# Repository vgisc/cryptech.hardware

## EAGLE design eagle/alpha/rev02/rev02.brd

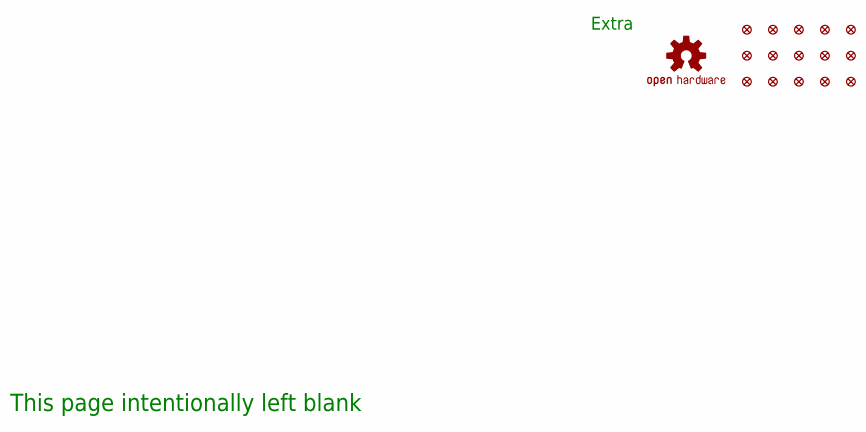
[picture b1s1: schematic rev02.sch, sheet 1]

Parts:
FID1, FID2, FID3, FID4, FID5, FID6, FID7, FID8, FID9, FID10, FID11, FID12, FID13, FID14, FID15: FIDUCIAL1X2; FIDUCIAL-1X2
LOGO1: OSHW-LOGOL-COPPER; OSHW-LOGO-L_COPPER

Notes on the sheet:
Extra
This page intentionally left blank

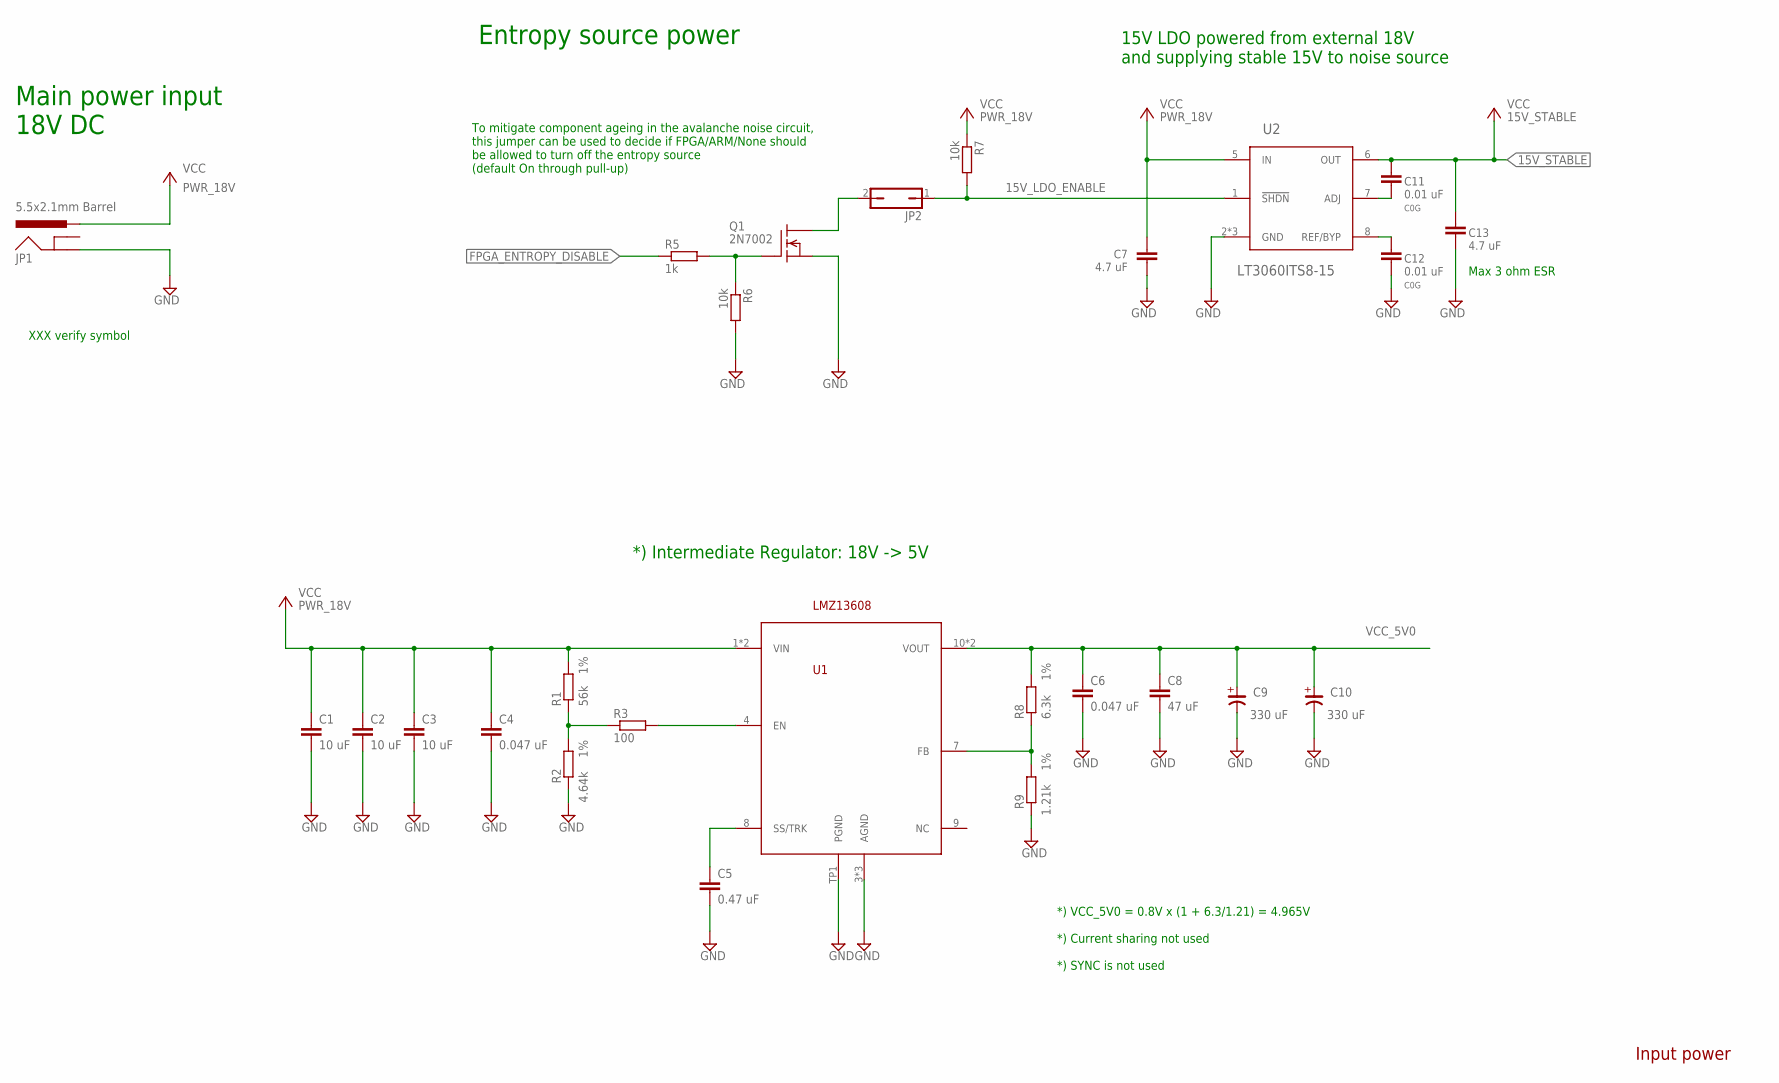
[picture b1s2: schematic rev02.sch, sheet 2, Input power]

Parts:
C1, C2, C3: 10 uF; C1210; TOLERANCE 10%
C4, C6: 0.047 uF; C0402; TOLERANCE 10%
C5: 0.47 uF; C0603; TOLERANCE 10%
C7, C13: 4.7 uF; C0603
C8: 47 uF; C1210; TOLERANCE 20%
C9, C10: 330 uF; CE-035X080; TOLERANCE 20%
C11, C12: 0.01 uF; C0402
JP1: 5.5x2.1mm Barrel; POWER_JACK_SMD
JP2: JP1Q; JP1
Q1: 2N7002; SOT23
R1: 56k; R0402; TOLERANCE 1%
R2: 4.64k; R0402; TOLERANCE 1%
R3: 100; R0402; TOLERANCE 5%
R5: 1k; R0402; TOLERANCE 5%
R6, R7: 10k; R0402; TOLERANCE 5%
R8: 6.3k; R0402; TOLERANCE 1%
R9: 1.21k; R0402; TOLERANCE 1%
U1: LMZ13608; NDY
U2: LT3060ITS8-15; TSOT-8-23

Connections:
15V_LDO_ENABLE: JP2.1, R7.2, U2.1 (!SHDN)
15V_STABLE: C11.2, C13.1, U2.6 (OUT); also elsewhere on the board
FPGA_ENTROPY_DISABLE: R5.1; also elsewhere on the board
GND: C1.2, C2.2, C3.2, C4.2, C5.2, C6.2, C7.2, C8.2, C9.-, C10.-, C12.1, C13.2, JP1.P$4 (GND), Q1.2 (S), R2.1, R6.2, R9.1, U1.3 (AGND), U1.5 (AGND), U1.6 (AGND), U1.TP1 (PGND), U2.2 (GND), U2.3 (GND), U2.4 (GND); also elsewhere on the board
unnamed: C11.1, U2.7 (ADJ)
unnamed: C12.2, U2.8 (REF/BYP)
unnamed: Q1.1 (G), R5.2, R6.1
unnamed: JP2.2, Q1.3 (D)
unnamed: C5.1, U1.8 (SS/TRK)
unnamed: R1.1, R2.2, R3.1
unnamed: R3.2, U1.4 (EN)
unnamed: R8.1, R9.2, U1.7 (FB)
PWR_18V: C1.1, C2.1, C3.1, C4.1, C7.1, JP1.VIN0 (PWR), R1.2, R7.1, U1.1 (VIN), U1.2 (VIN), U2.5 (IN)
VCC_5V0: C6.1, C8.1, C9.+, C10.+, R8.2, U1.10 (VOUT), U1.11 (VOUT); also elsewhere on the board

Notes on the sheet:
15V LDO powered from external 18V and supplying stable 15V to noise source
Main power input 18V DC
To mitigate component ageing in the avalanche noise circuit, this jumper can be used to decide if FPGA/ARM/None should be allowed to turn off the entropy source (default On through pull-up)
Max 3 ohm ESR
*) Intermediate Regulator: 18V -> 5V
*) VCC_5V0 = 0.8V x (1 + 6.3/1.21) = 4.965V *) Current sharing not used *) SYNC is not used
Entropy source power
XXX verify symbol
Input power

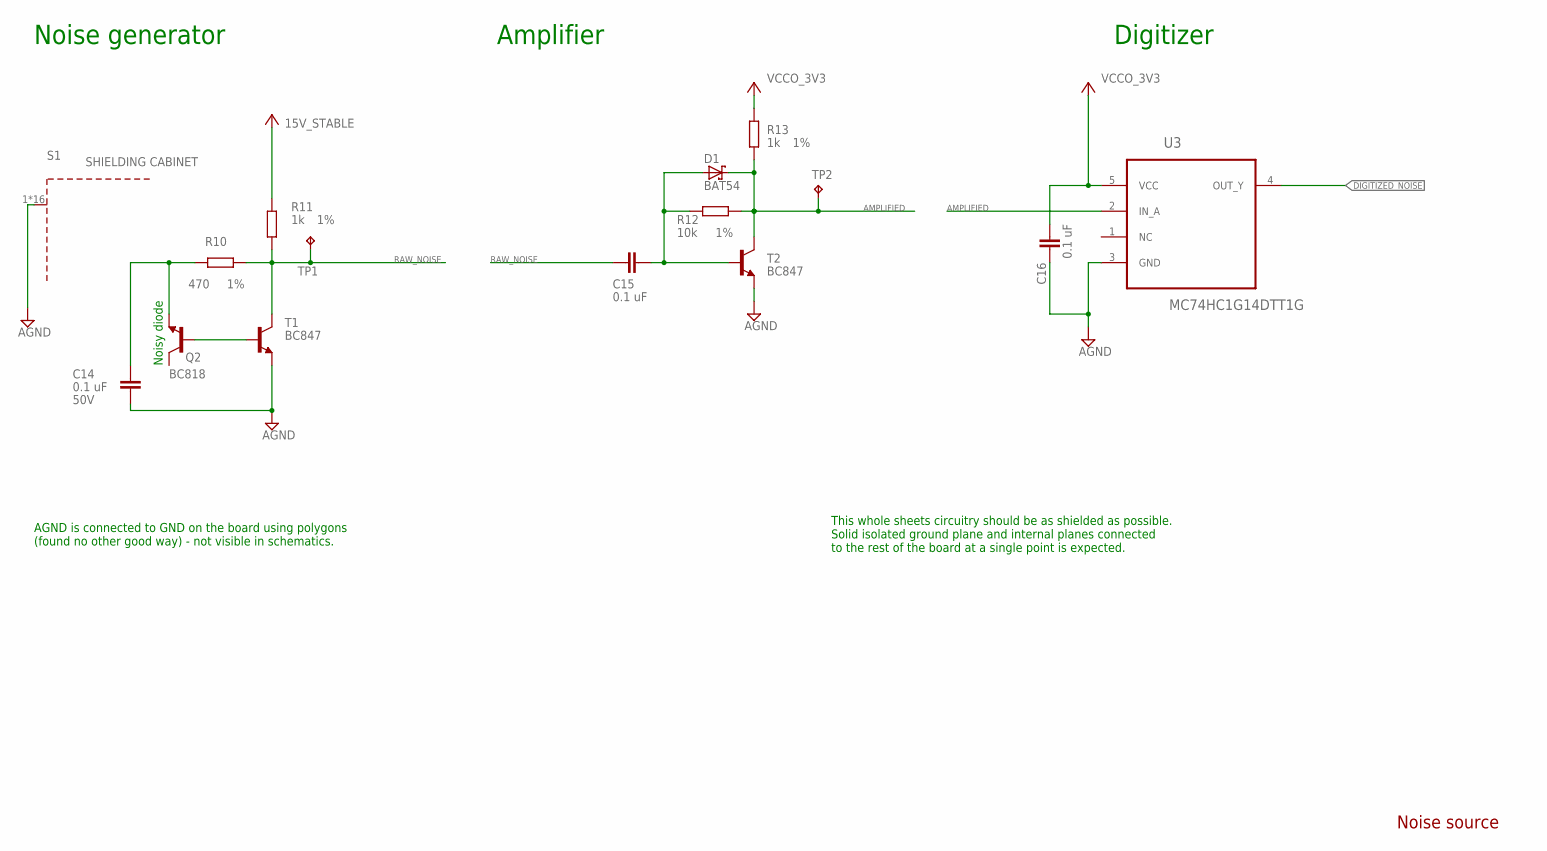
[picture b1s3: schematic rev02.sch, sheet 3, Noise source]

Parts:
C14, C15, C16: 0.1 uF; C0603; TOLERANCE 10%
D1: BAT54; SOT23
Q2: BC818; SOT23-BEC
R10: 470; R0402; TOLERANCE 1%
R11, R13: 1k; R0402; TOLERANCE 1%
R12: 10k; R0402; TOLERANCE 1%
S1: SHIELDING CABINET; WE-SHC_36103205_NO_CREAM
T1, T2: BC847; SOT23
TP1, TP2: TPB1,27; B1,27
U3: MC74HC1G14DTT1G; SOT95P275X110-5N

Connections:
15V_STABLE: R11.1; also elsewhere on the board
AGND: C16.1, S1.1, S1.2, S1.3, S1.4, S1.5, S1.6, S1.7, S1.8, S1.9, S1.10, S1.11, S1.12, S1.13, S1.14, S1.15, S1.16, T2.2 (E), U3.3 (GND)
AMPLIFIED: D1.3 (C), R12.2, R13.1, T2.3 (C), TP2.TP, U3.2 (IN_A)
AMP_P1: C15.2, D1.1 (A), R12.1, T2.1 (B)
DIGITIZED_NOISE: U3.4 (OUT_Y); also elsewhere on the board
GND: C14.1, T1.2 (E); also elsewhere on the board
NOISE_IN: C14.2, Q2.E, R10.2
NOISE_OUT: Q2.B, T1.1 (B)
RAW_NOISE: C15.1, R10.1, R11.2, T1.3 (C), TP1.TP
VCCO_3V3: C16.2, R13.2, U3.5 (VCC); also elsewhere on the board

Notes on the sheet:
Digitizer
Noise generator
Noisy diode
Amplifier
AGND is connected to GND on the board using polygons (found no other good way) - not visible in schematics.
This whole sheets circuitry should be as shielded as possible. Solid isolated ground plane and internal planes connected to the rest of the board at a single point is expected.
Noise source

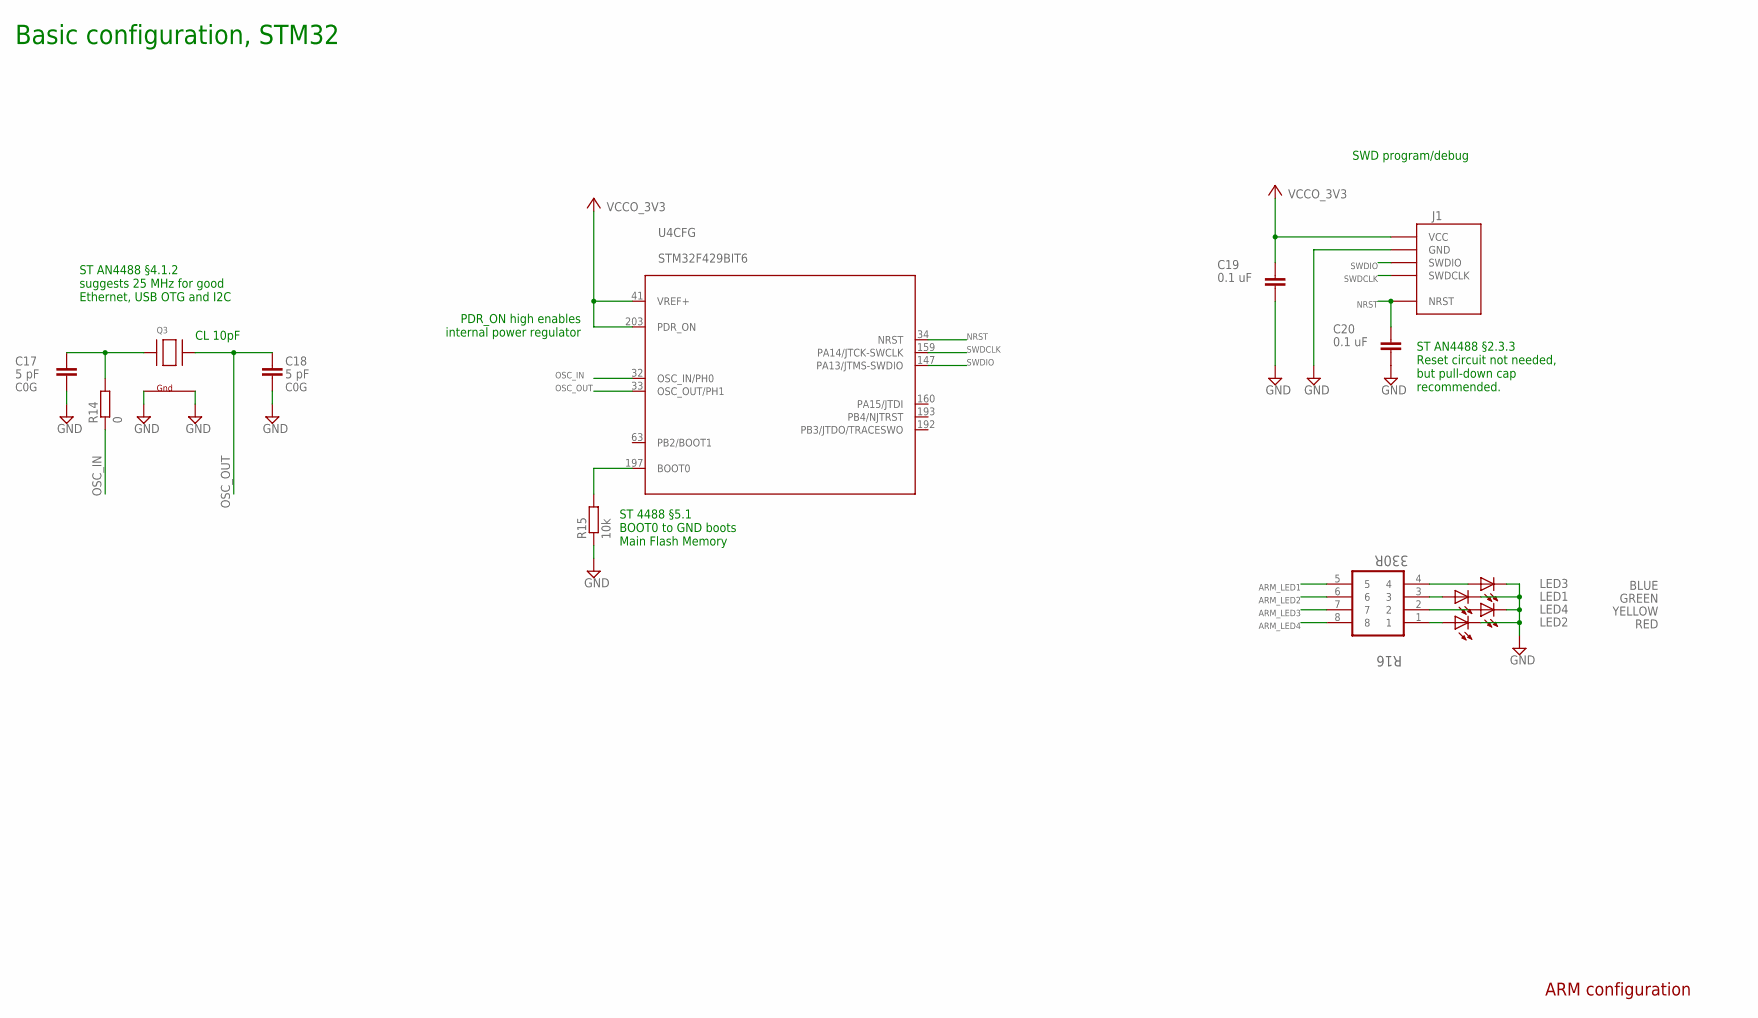
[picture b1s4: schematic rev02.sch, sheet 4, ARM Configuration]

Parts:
C17, C18: 5 pF; C0402
C19, C20: 0.1 uF; C0402
J1: STM32-SWD; 100MIL_THT
LED1: GREEN; CHIP-LED0603
LED2: RED; CHIP-LED0603
LED3: BLUE; CHIP-LED0603
LED4: YELLOW; CHIP-LED0603
Q3: XTAL-4-3225; NX3225; MPN ABM8G-25.000MHZ-4Y-T3
R14: 0; R0402
R15: 10k; R0402; TOLERANCE 5%
R16: 330R; RESCAXE80P320X160X60-8N
U4: STM32F429BIT6; LQFP-208

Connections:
ARM_LED1: R16.5; also elsewhere on the board
ARM_LED2: R16.6; also elsewhere on the board
ARM_LED3: R16.7; also elsewhere on the board
ARM_LED4: R16.8; also elsewhere on the board
BOOT0: R15.2, U4.197 (BOOT0)
GND: C17.1, C18.1, C19.2, C20.2, J1.P$GND (GND), LED1.C, LED2.C, LED3.C, LED4.C, Q3.2 (G2), Q3.4 (G1), R15.1; also elsewhere on the board
unnamed: LED3.A, R16.4
unnamed: LED1.A, R16.3
unnamed: LED4.A, R16.2
unnamed: LED2.A, R16.1
unnamed: C17.2, Q3.1 (X1), R14.2
NRST: C20.1, J1.P$NRST (NRST), U4.34 (NRST)
OSC_IN: R14.1, U4.32 (OSC_IN/PH0)
OSC_OUT: C18.2, Q3.3 (X2), U4.33 (OSC_OUT/PH1)
SWDCLK: J1.P$SWDCLK (SWDCLK), U4.159 (PA14/JTCK-SWCLK)
SWDIO: J1.P$SWDIO (SWDIO), U4.147 (PA13/JTMS-SWDIO)
VCCO_3V3: C19.1, J1.P$VCC (VCC), U4.41 (VREF+), U4.203 (PDR_ON); also elsewhere on the board

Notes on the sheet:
ST 4488 §5.1 BOOT0 to GND boots Main Flash Memory
ST AN4488 §4.1.2 suggests 25 MHz for good Ethernet, USB OTG and I2C
SWD program/debug
ST AN4488 §2.3.3 Reset circuit not needed, but pull-down cap recommended.
PDR_ON high enables internal power regulator
CL 10pF
Basic configuration, STM32
ARM configuration

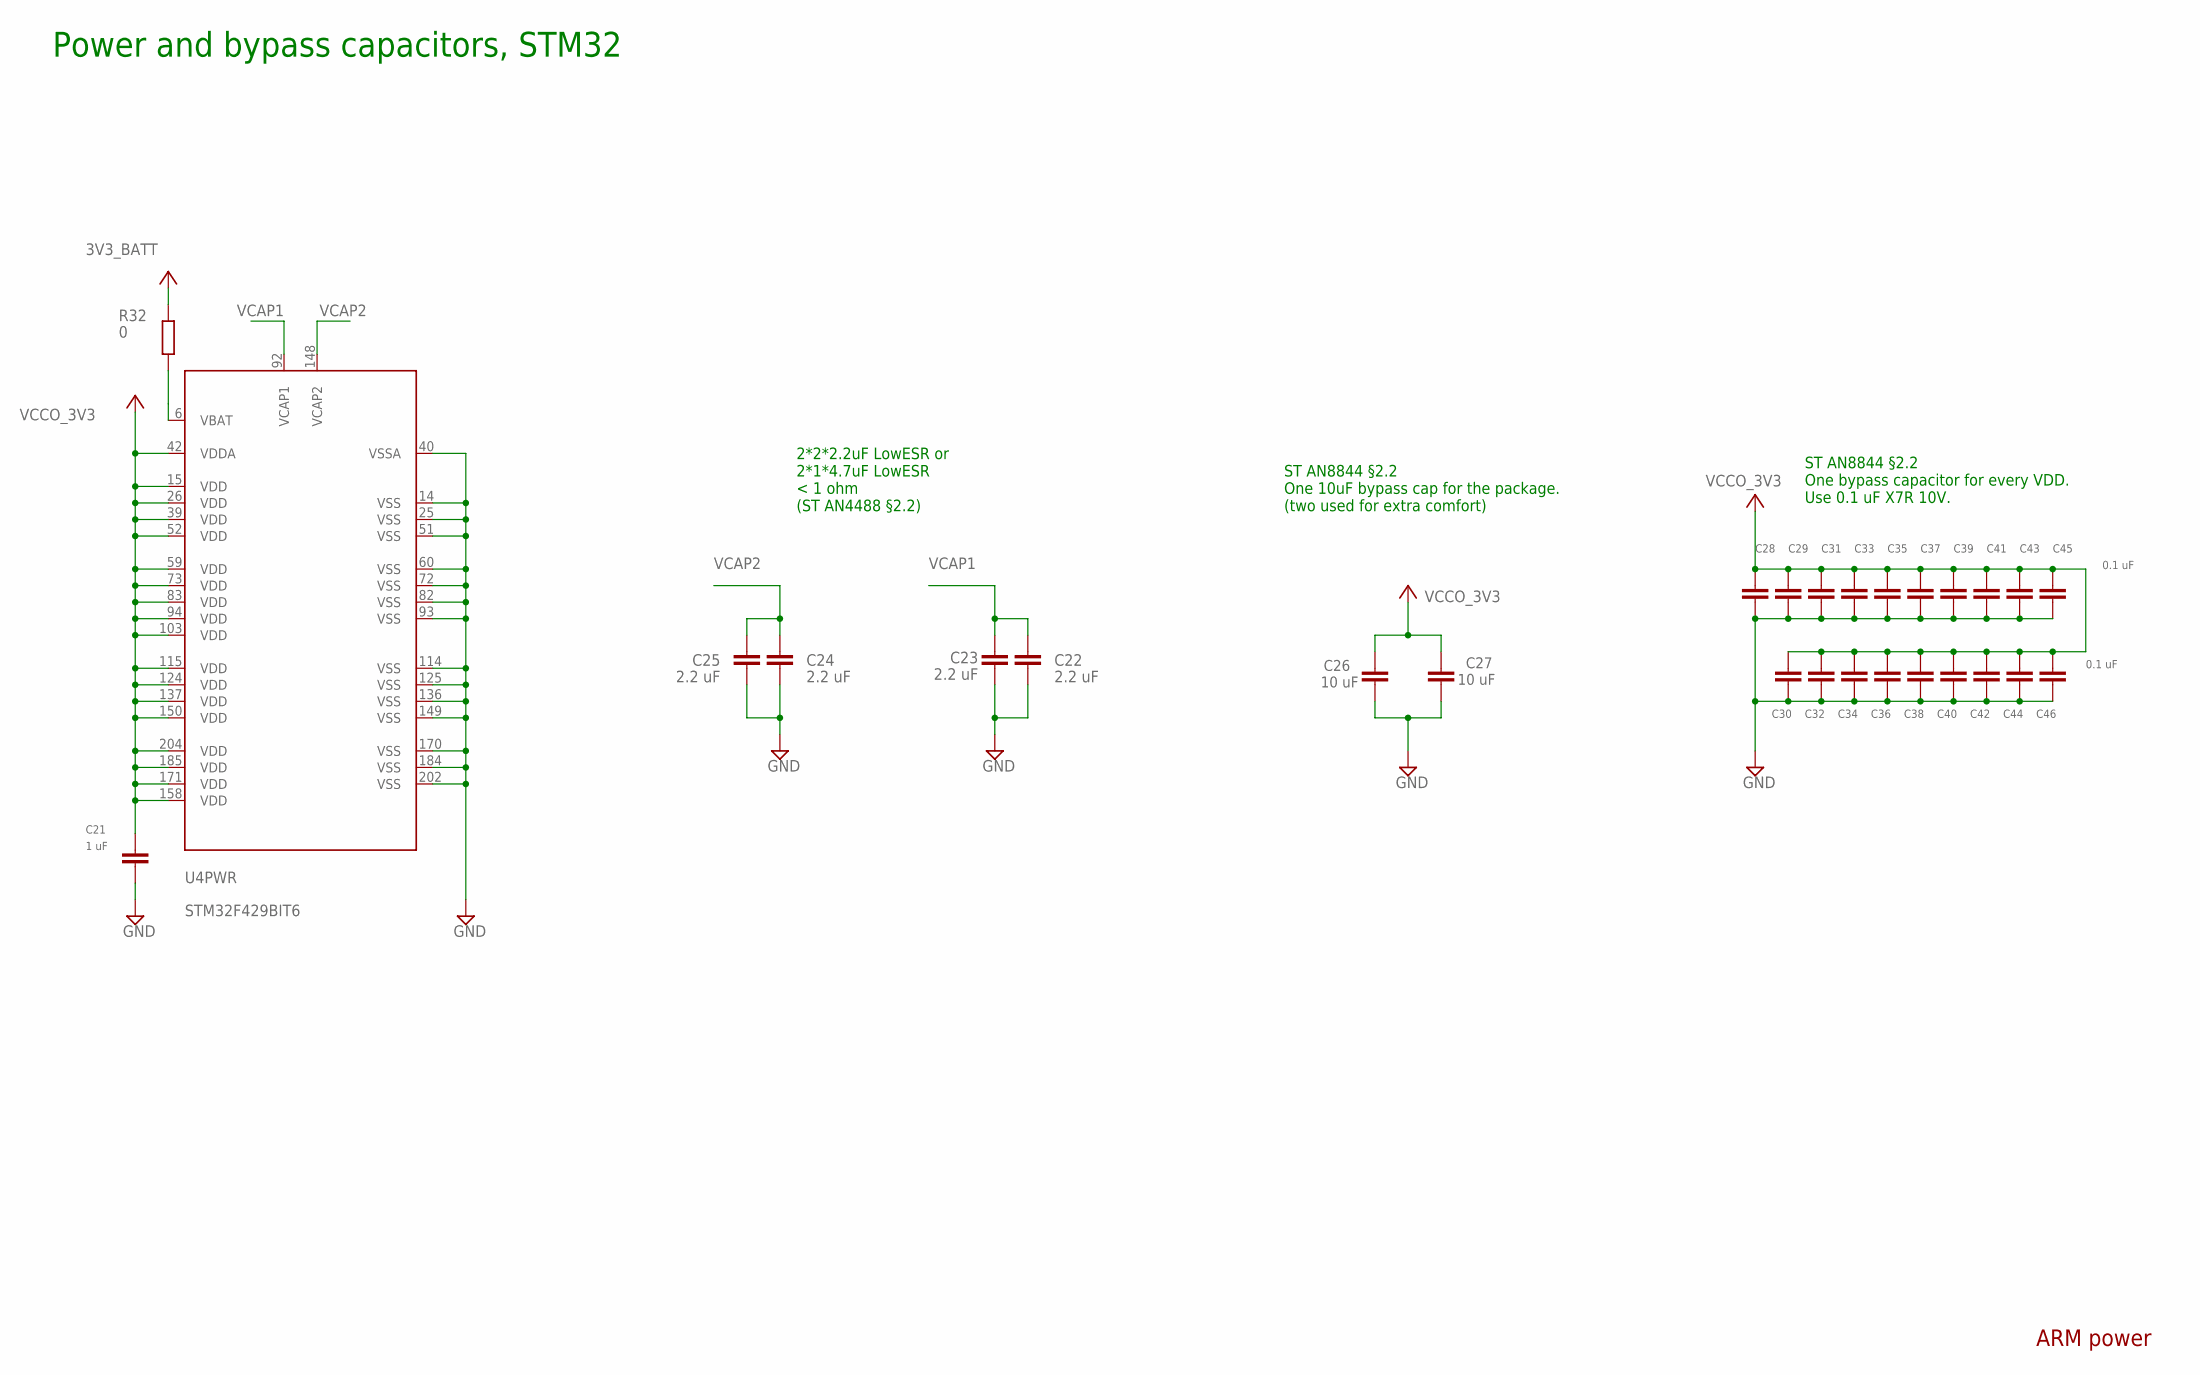
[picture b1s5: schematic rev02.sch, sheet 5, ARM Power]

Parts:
C21: 1 uF; C0603
C22, C23, C24, C25: 2.2 uF; C0603
C26, C27: 10 uF; C0805
C28, C29, C30, C31, C32, C33, C34, C35, C36, C37, C38, C39, C40, C41, C42, C43, C44, C45, C46: 0.1 uF; C0402
R32: 0; R0402; TOLERANCE 5%
U4: STM32F429BIT6; LQFP-208

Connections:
3V3_BATT: R32.1; also elsewhere on the board
GND: C21.2, C22.1, C23.1, C24.1, C25.1, C26.2, C27.2, C28.2, C29.2, C30.2, C31.2, C32.2, C33.2, C34.2, C35.2, C36.2, C37.2, C38.2, C39.2, C40.2, C41.2, C42.2, C43.2, C44.2, C45.2, C46.2, U4.14 (VSS), U4.25 (VSS), U4.40 (VSSA), U4.51 (VSS), U4.60 (VSS), U4.72 (VSS), U4.82 (VSS), U4.93 (VSS), U4.114 (VSS), U4.125 (VSS), U4.136 (VSS), U4.149 (VSS), U4.170 (VSS), U4.184 (VSS), U4.202 (VSS); also elsewhere on the board
VCAP1: C22.2, C23.2, U4.92 (VCAP1)
VCAP2: C24.2, C25.2, U4.148 (VCAP2)
VCCO_3V3: C21.1, C26.1, C27.1, C28.1, C29.1, C30.1, C31.1, C32.1, C33.1, C34.1, C35.1, C36.1, C37.1, C38.1, C39.1, C40.1, C41.1, C42.1, C43.1, C44.1, C45.1, C46.1, U4.15 (VDD), U4.26 (VDD), U4.39 (VDD), U4.42 (VDDA), U4.52 (VDD), U4.59 (VDD), U4.73 (VDD), U4.83 (VDD), U4.94 (VDD), U4.103 (VDD), U4.115 (VDD), U4.124 (VDD), U4.137 (VDD), U4.150 (VDD), U4.158 (VDD), U4.171 (VDD), U4.185 (VDD), U4.204 (VDD); also elsewhere on the board

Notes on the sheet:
ST AN8844 §2.2 One bypass capacitor for every VDD. Use 0.1 uF X7R 10V.
ST AN8844 §2.2 One 10uF bypass cap for the package. (two used for extra comfort)
2*2*2.2uF LowESR or 2*1*4.7uF LowESR < 1 ohm (ST AN4488 §2.2)
Power and bypass capacitors, STM32
ARM power

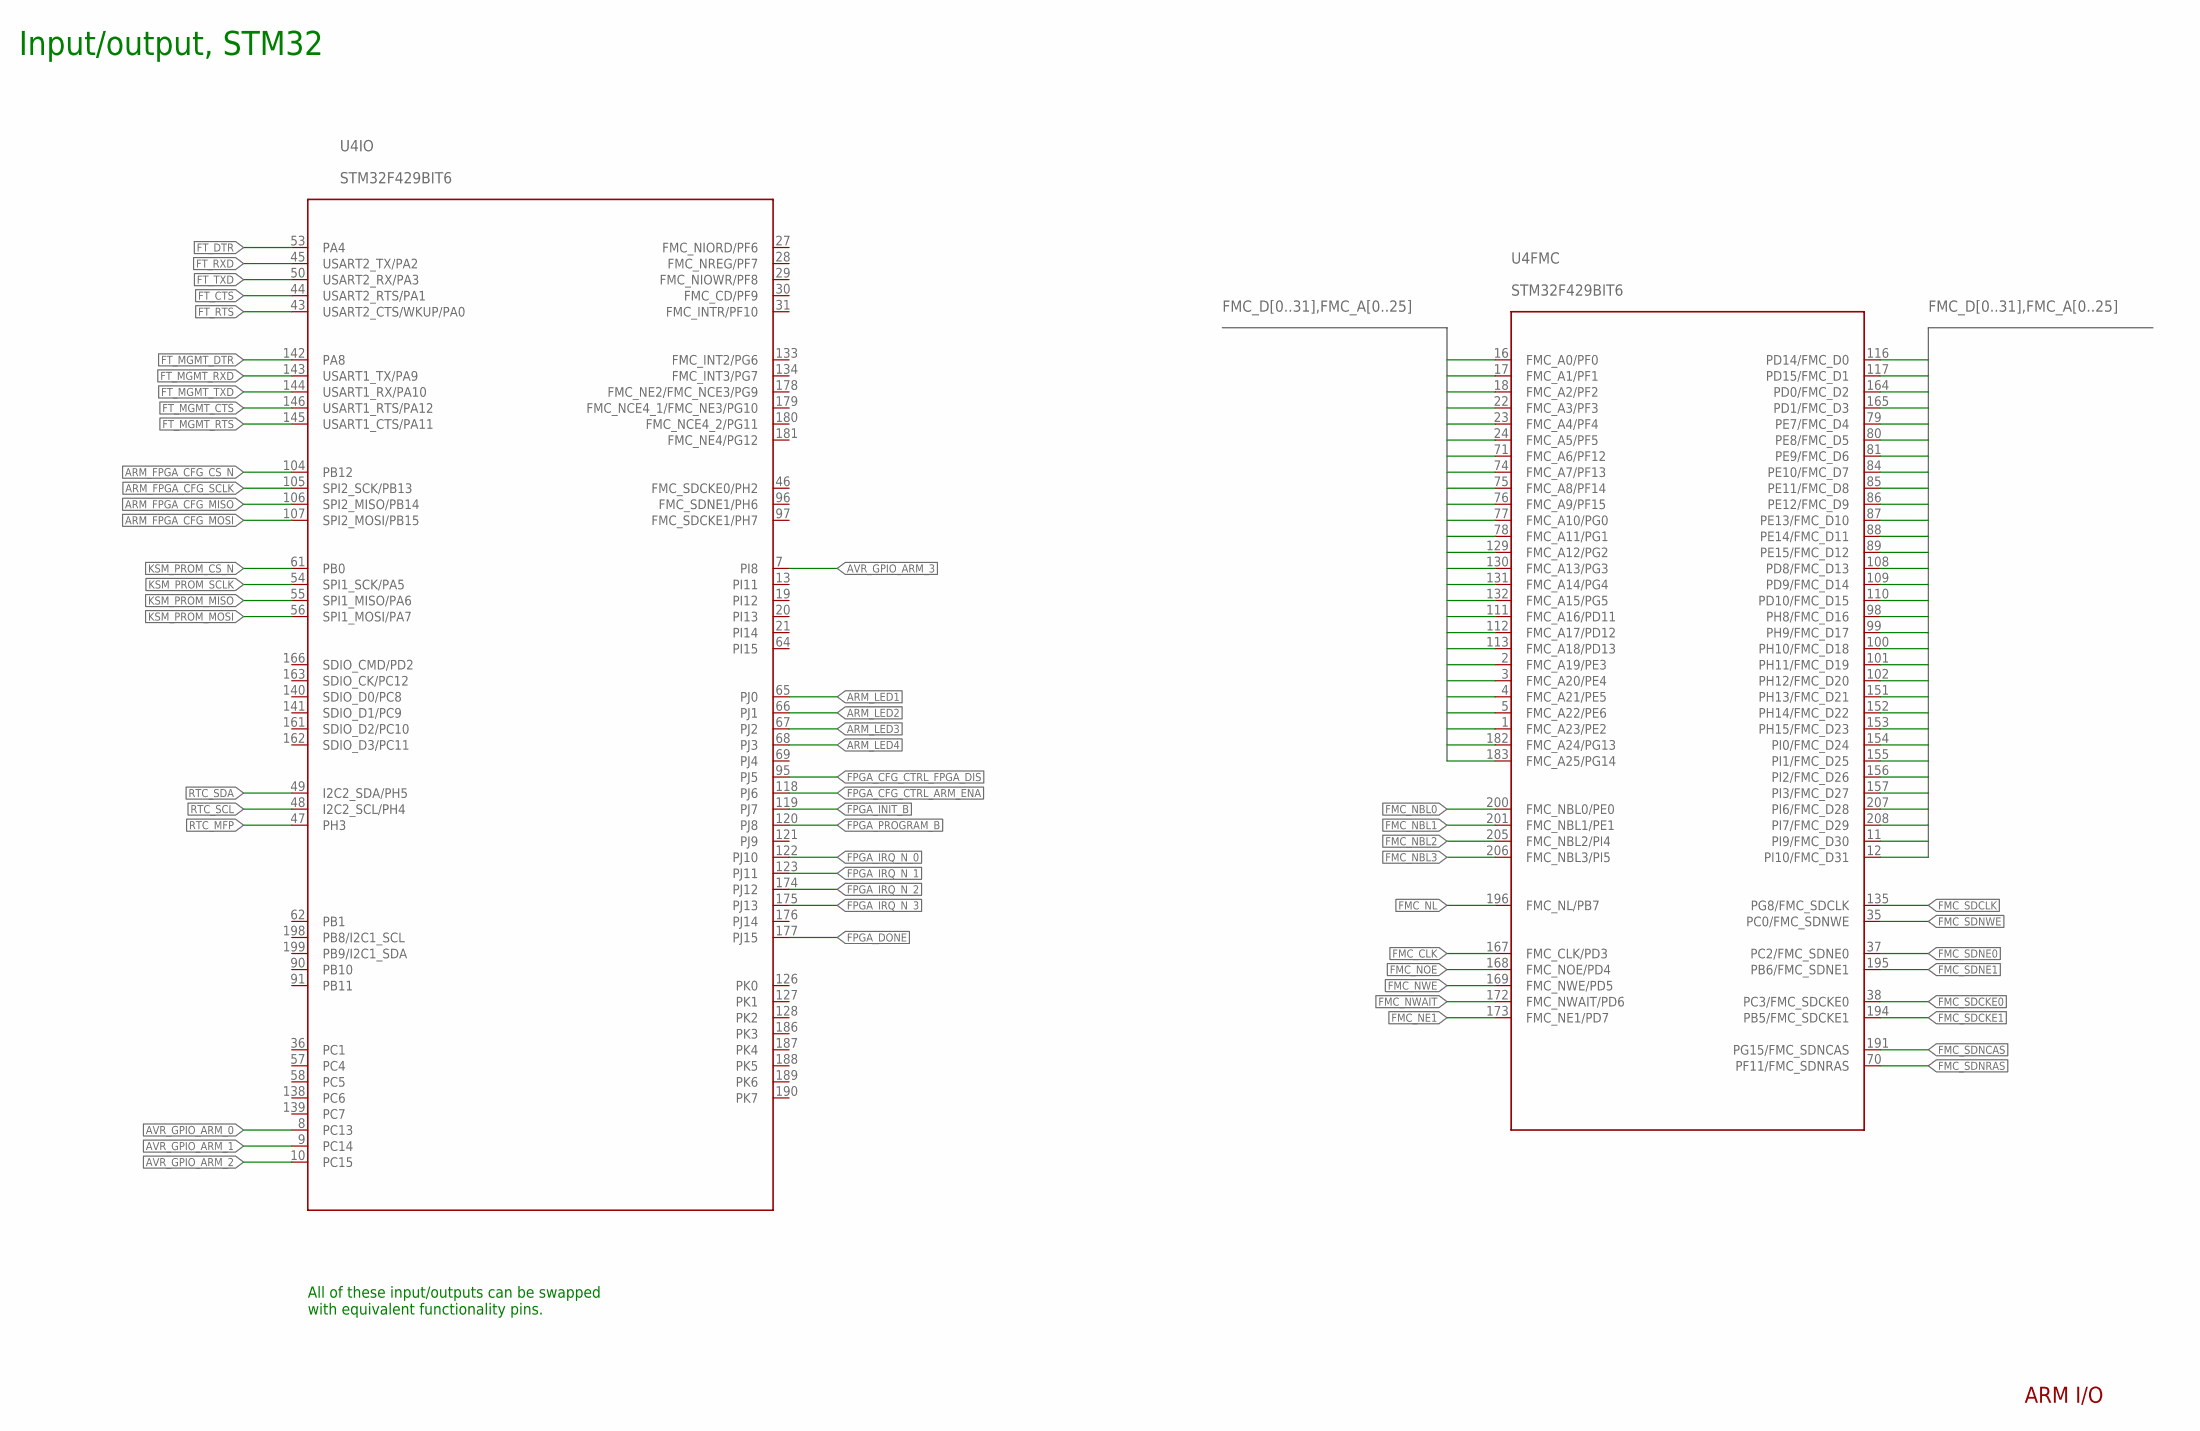
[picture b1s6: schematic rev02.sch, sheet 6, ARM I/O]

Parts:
U4: STM32F429BIT6; LQFP-208

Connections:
ARM_FPGA_CFG_CS_N: U4.104 (PB12); also elsewhere on the board
ARM_FPGA_CFG_MISO: U4.106 (SPI2_MISO/PB14); also elsewhere on the board
ARM_FPGA_CFG_MOSI: U4.107 (SPI2_MOSI/PB15); also elsewhere on the board
ARM_FPGA_CFG_SCLK: U4.105 (SPI2_SCK/PB13); also elsewhere on the board
ARM_LED1: U4.65 (PJ0); also elsewhere on the board
ARM_LED2: U4.66 (PJ1); also elsewhere on the board
ARM_LED3: U4.67 (PJ2); also elsewhere on the board
ARM_LED4: U4.68 (PJ3); also elsewhere on the board
AVR_GPIO_ARM_0: U4.8 (PC13); also elsewhere on the board
AVR_GPIO_ARM_1: U4.9 (PC14); also elsewhere on the board
FMC_A0: U4.16 (FMC_A0/PF0); also elsewhere on the board
FMC_A1: U4.17 (FMC_A1/PF1); also elsewhere on the board
FMC_A2: U4.18 (FMC_A2/PF2); also elsewhere on the board
FMC_A3: U4.22 (FMC_A3/PF3); also elsewhere on the board
FMC_A4: U4.23 (FMC_A4/PF4); also elsewhere on the board
FMC_A5: U4.24 (FMC_A5/PF5); also elsewhere on the board
FMC_A6: U4.71 (FMC_A6/PF12); also elsewhere on the board
FMC_A7: U4.74 (FMC_A7/PF13); also elsewhere on the board
FMC_A8: U4.75 (FMC_A8/PF14); also elsewhere on the board
FMC_A9: U4.76 (FMC_A9/PF15); also elsewhere on the board
FMC_A10: U4.77 (FMC_A10/PG0); also elsewhere on the board
FMC_A11: U4.78 (FMC_A11/PG1); also elsewhere on the board
FMC_A12: U4.129 (FMC_A12/PG2); also elsewhere on the board
FMC_A13: U4.130 (FMC_A13/PG3); also elsewhere on the board
FMC_A14: U4.131 (FMC_A14/PG4); also elsewhere on the board
FMC_A15: U4.132 (FMC_A15/PG5); also elsewhere on the board
FMC_A16: U4.111 (FMC_A16/PD11); also elsewhere on the board
FMC_A17: U4.112 (FMC_A17/PD12); also elsewhere on the board
FMC_A18: U4.113 (FMC_A18/PD13); also elsewhere on the board
FMC_A19: U4.2 (FMC_A19/PE3); also elsewhere on the board
FMC_A20: U4.3 (FMC_A20/PE4); also elsewhere on the board
FMC_A21: U4.4 (FMC_A21/PE5); also elsewhere on the board
FMC_A22: U4.5 (FMC_A22/PE6); also elsewhere on the board
FMC_A23: U4.1 (FMC_A23/PE2); also elsewhere on the board
FMC_A24: U4.182 (FMC_A24/PG13); also elsewhere on the board
FMC_A25: U4.183 (FMC_A25/PG14); also elsewhere on the board
FMC_CLK: U4.167 (FMC_CLK/PD3); also elsewhere on the board
FMC_D0: U4.116 (PD14/FMC_D0); also elsewhere on the board
FMC_D1: U4.117 (PD15/FMC_D1); also elsewhere on the board
FMC_D2: U4.164 (PD0/FMC_D2); also elsewhere on the board
FMC_D3: U4.165 (PD1/FMC_D3); also elsewhere on the board
FMC_D4: U4.79 (PE7/FMC_D4); also elsewhere on the board
FMC_D5: U4.80 (PE8/FMC_D5); also elsewhere on the board
FMC_D6: U4.81 (PE9/FMC_D6); also elsewhere on the board
FMC_D7: U4.84 (PE10/FMC_D7); also elsewhere on the board
FMC_D8: U4.85 (PE11/FMC_D8); also elsewhere on the board
FMC_D9: U4.86 (PE12/FMC_D9); also elsewhere on the board
FMC_D10: U4.87 (PE13/FMC_D10); also elsewhere on the board
FMC_D11: U4.88 (PE14/FMC_D11); also elsewhere on the board
FMC_D12: U4.89 (PE15/FMC_D12); also elsewhere on the board
FMC_D13: U4.108 (PD8/FMC_D13); also elsewhere on the board
FMC_D14: U4.109 (PD9/FMC_D14); also elsewhere on the board
FMC_D15: U4.110 (PD10/FMC_D15); also elsewhere on the board
FMC_D16: U4.98 (PH8/FMC_D16); also elsewhere on the board
FMC_D17: U4.99 (PH9/FMC_D17); also elsewhere on the board
FMC_D18: U4.100 (PH10/FMC_D18); also elsewhere on the board
FMC_D19: U4.101 (PH11/FMC_D19); also elsewhere on the board
FMC_D20: U4.102 (PH12/FMC_D20); also elsewhere on the board
FMC_D21: U4.151 (PH13/FMC_D21); also elsewhere on the board
FMC_D22: U4.152 (PH14/FMC_D22); also elsewhere on the board
FMC_D23: U4.153 (PH15/FMC_D23); also elsewhere on the board
FMC_D24: U4.154 (PI0/FMC_D24); also elsewhere on the board
FMC_D25: U4.155 (PI1/FMC_D25); also elsewhere on the board
FMC_D26: U4.156 (PI2/FMC_D26); also elsewhere on the board
FMC_D27: U4.157 (PI3/FMC_D27); also elsewhere on the board
FMC_D28: U4.207 (PI6/FMC_D28); also elsewhere on the board
FMC_D29: U4.208 (PI7/FMC_D29); also elsewhere on the board
FMC_D30: U4.11 (PI9/FMC_D30); also elsewhere on the board
FMC_D31: U4.12 (PI10/FMC_D31); also elsewhere on the board
FMC_NBL0: U4.200 (FMC_NBL0/PE0); also elsewhere on the board
FMC_NBL1: U4.201 (FMC_NBL1/PE1); also elsewhere on the board
FMC_NBL2: U4.205 (FMC_NBL2/PI4); also elsewhere on the board
FMC_NBL3: U4.206 (FMC_NBL3/PI5); also elsewhere on the board
FMC_NE1: U4.173 (FMC_NE1/PD7); also elsewhere on the board
FMC_NL: U4.196 (FMC_NL/PB7); also elsewhere on the board
FMC_NOE: U4.168 (FMC_NOE/PD4); also elsewhere on the board
FMC_NWAIT: U4.172 (FMC_NWAIT/PD6); also elsewhere on the board
FMC_NWE: U4.169 (FMC_NWE/PD5); also elsewhere on the board
FMC_SDCKE0: U4.38 (PC3/FMC_SDCKE0); also elsewhere on the board
FMC_SDCKE1: U4.194 (PB5/FMC_SDCKE1); also elsewhere on the board
FMC_SDCLK: U4.135 (PG8/FMC_SDCLK); also elsewhere on the board
FMC_SDNCAS: U4.191 (PG15/FMC_SDNCAS); also elsewhere on the board
FMC_SDNE0: U4.37 (PC2/FMC_SDNE0); also elsewhere on the board
FMC_SDNE1: U4.195 (PB6/FMC_SDNE1); also elsewhere on the board
FMC_SDNRAS: U4.70 (PF11/FMC_SDNRAS); also elsewhere on the board
FMC_SDNWE: U4.35 (PC0/FMC_SDNWE); also elsewhere on the board
FPGA_CFG_CTRL_ARM_ENA: U4.118 (PJ6); also elsewhere on the board
FPGA_CFG_CTRL_FPGA_DIS: U4.95 (PJ5); also elsewhere on the board
FPGA_DONE: U4.177 (PJ15); also elsewhere on the board
FPGA_INIT_B: U4.119 (PJ7); also elsewhere on the board
FPGA_IRQ_N_0: U4.122 (PJ10); also elsewhere on the board
FPGA_IRQ_N_1: U4.123 (PJ11); also elsewhere on the board
FPGA_IRQ_N_2: U4.174 (PJ12); also elsewhere on the board
FPGA_IRQ_N_3: U4.175 (PJ13); also elsewhere on the board
FPGA_PROGRAM_B: U4.120 (PJ8); also elsewhere on the board
FT_CTS: U4.44 (USART2_RTS/PA1); also elsewhere on the board
FT_DTR: U4.53 (PA4); also elsewhere on the board
FT_MGMT_CTS: U4.146 (USART1_RTS/PA12); also elsewhere on the board
FT_MGMT_DTR: U4.142 (PA8); also elsewhere on the board
FT_MGMT_RTS: U4.145 (USART1_CTS/PA11); also elsewhere on the board
FT_MGMT_RXD: U4.143 (USART1_TX/PA9); also elsewhere on the board
FT_MGMT_TXD: U4.144 (USART1_RX/PA10); also elsewhere on the board
FT_RTS: U4.43 (USART2_CTS/WKUP/PA0); also elsewhere on the board
FT_RXD: U4.45 (USART2_TX/PA2); also elsewhere on the board
FT_TXD: U4.50 (USART2_RX/PA3); also elsewhere on the board
KSM_PROM_CS_N: U4.61 (PB0); also elsewhere on the board
KSM_PROM_MISO: U4.55 (SPI1_MISO/PA6); also elsewhere on the board
KSM_PROM_MOSI: U4.56 (SPI1_MOSI/PA7); also elsewhere on the board
KSM_PROM_SCLK: U4.54 (SPI1_SCK/PA5); also elsewhere on the board
RTC_MFP: U4.47 (PH3); also elsewhere on the board
RTC_SCL: U4.48 (I2C2_SCL/PH4); also elsewhere on the board
RTC_SDA: U4.49 (I2C2_SDA/PH5); also elsewhere on the board

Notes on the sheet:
All of these input/outputs can be swapped with equivalent functionality pins.
Input/output, STM32
ARM I/O

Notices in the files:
parts and their libraries:
SparkFun-Aesthetics: Licensing: Creative Commons ShareAlike 4.0 International - https://creativecommons.org/licenses/by-sa/4.0
microbuilder: This work is placed in the public domain, and may be freely used for commercial and non-commercial work with the following conditions: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
